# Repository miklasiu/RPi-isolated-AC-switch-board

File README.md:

# RPi isolated AC switch board
 24/110/230V AC triac switch board

The board is intended to be used as a garden watering control be me. Use for whatever you want yourselves. 
There is Python based software being developed thar runs on this hardware.
I used optotriac-trac because it is ~3 times less expenssive than cheapest relay and it should outlast any realy.
Triac introduces ~1.4V drop but it doesn't matter much for 24V and is negligible for 110V and up.

Borard can be made at home as a 1 side. All top-side connections can be made with wires. This is the way I did it.
For the Triac you can use BTA312. I was worried they won't trigger correctly with low voltage/current but they do without a problem.
I used BTA312-600 from WeEn but any low gate current, high voltage triac will likely work.

High side 10nF capacitor needs to be rated to peak-to-peak voltage (RMS_ACV*1.41). I used 500V ones.

I didn't use I2C eeprom at all. It was intended for RPi HAT configuration, but it works without it.

You can omit indicator LEDs and their resistors too.

Generally I put too much stuff here.

Oh there are 8 inputs for whatever use you wish inteded for dry contacts. NO VOLTAGE - just switches/contacts (water level, pressure)
And I2C connector with pinout for 0.91" OLED module. I don't use it too :).

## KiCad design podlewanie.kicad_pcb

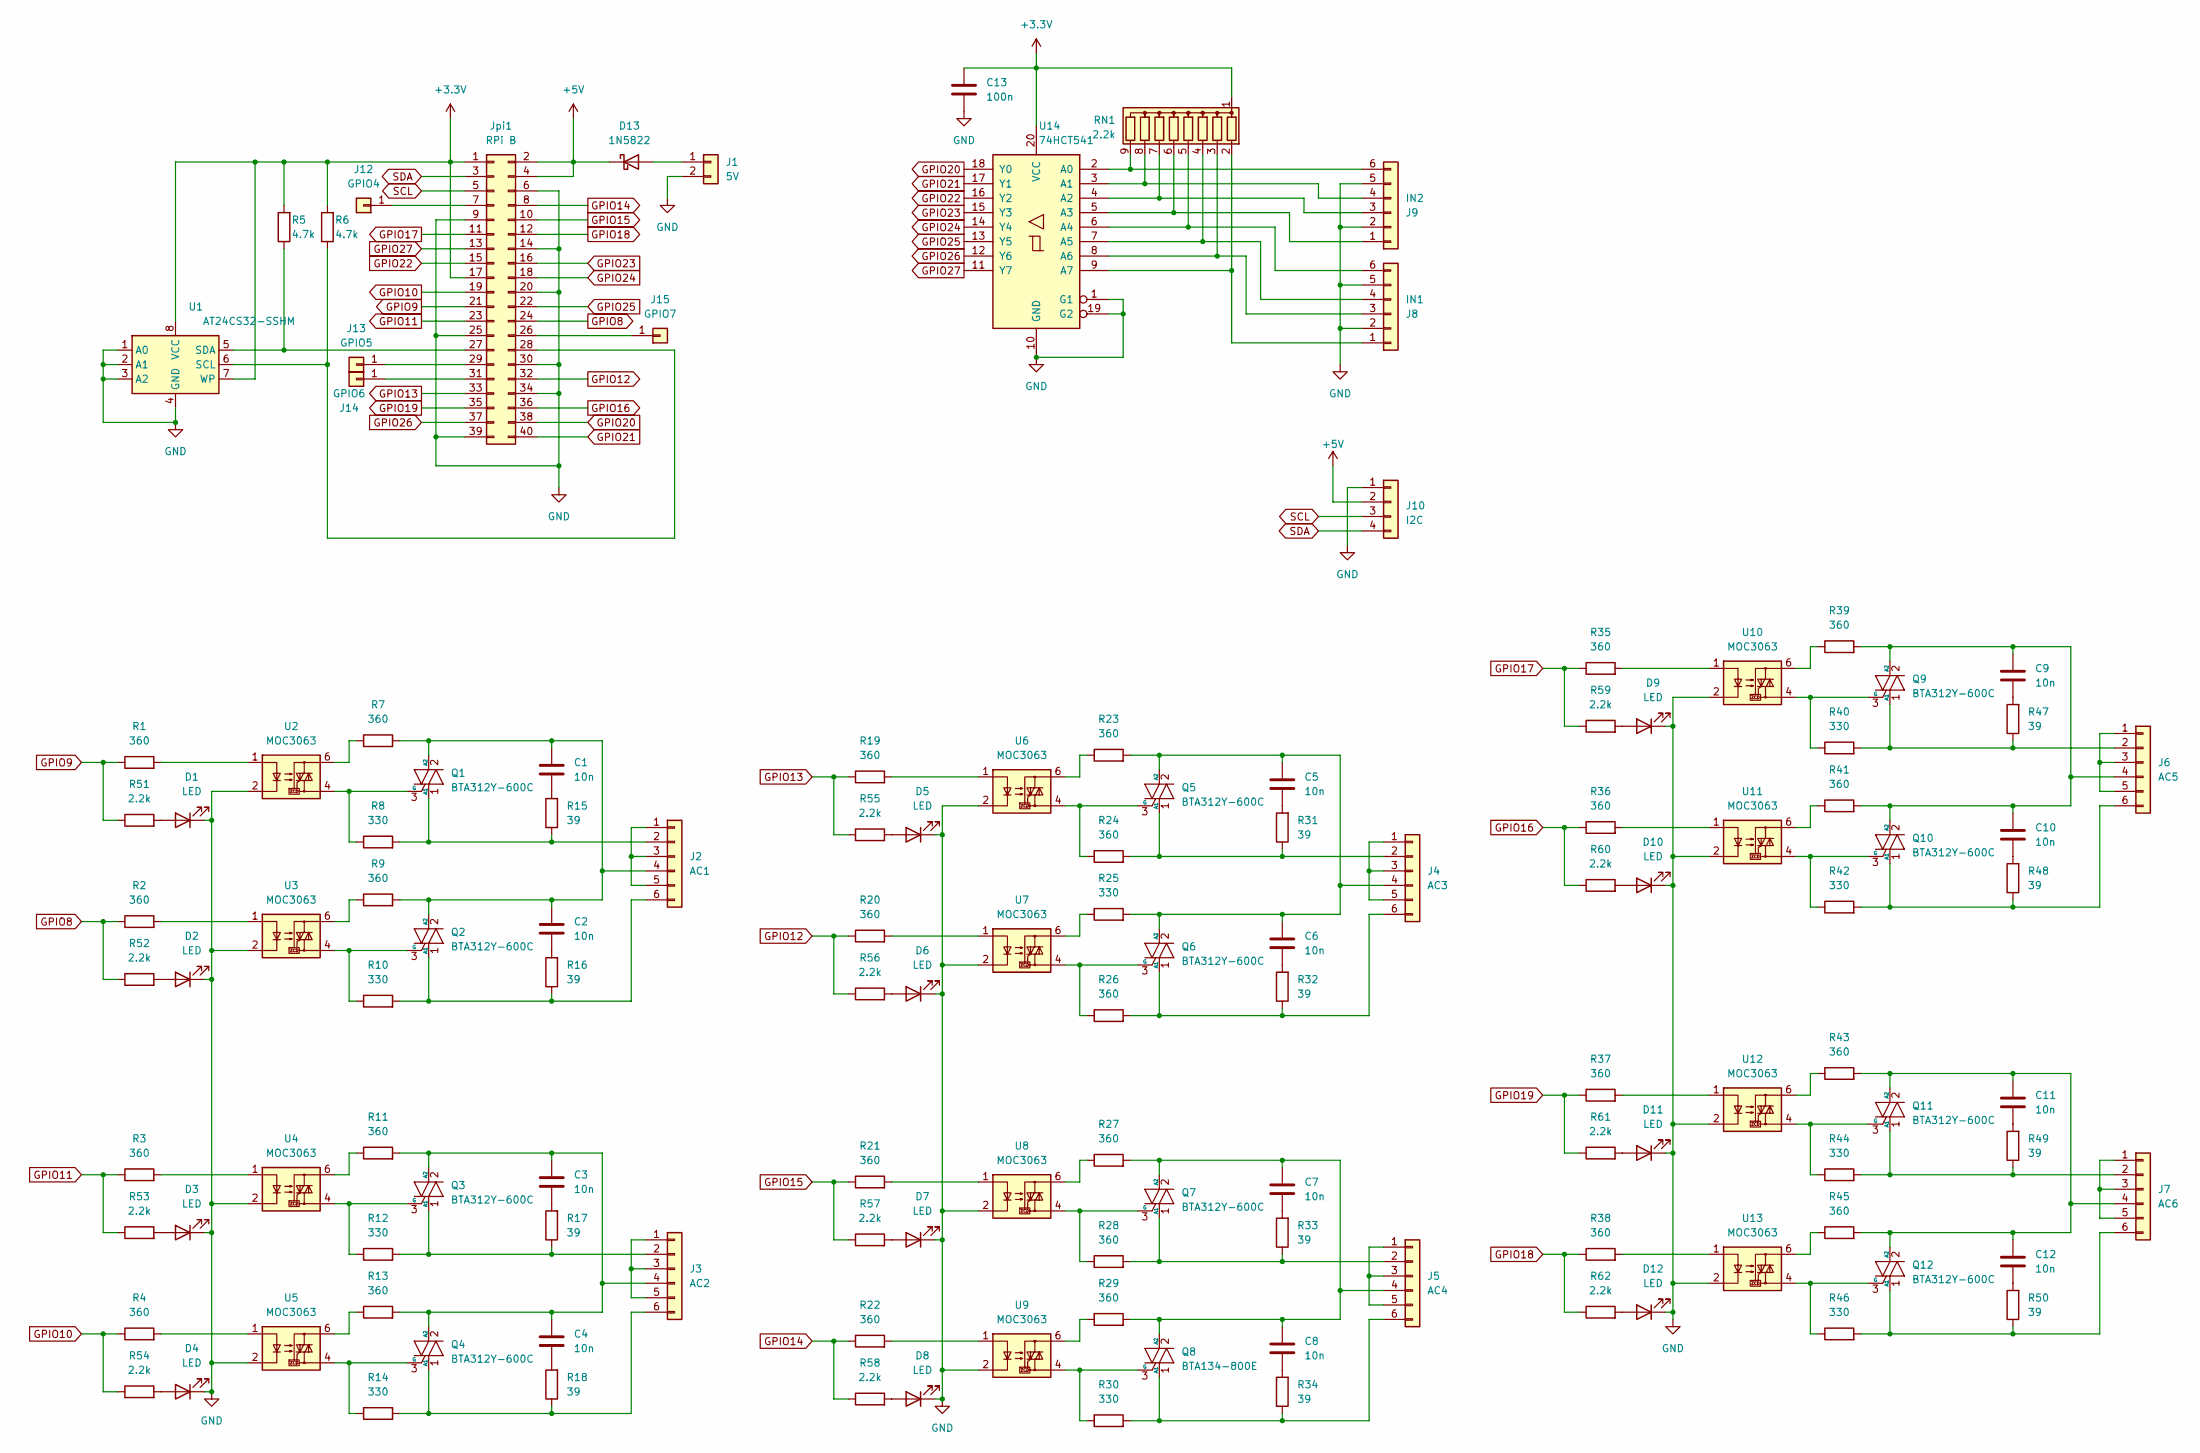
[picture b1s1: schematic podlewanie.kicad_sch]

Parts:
C1, C2, C3, C4, C5, C6, C7, C8, C9, C10, C11, C12: 10n; C_Disc_D9.0mm_W2.5mm_P5.00mm
C13: 100n; C_1206_3216Metric_Pad1.33x1.80mm_HandSolder
D1, D2, D3, D4, D5, D6, D7, D8, D9, D10, D11, D12: LED; LED_D3.0mm
D13: 1N5822; D_DO-201AD_P15.24mm_Horizontal
J1: 5V; Wago_734-162_1x02_P3.50mm_Horizontal
J2: AC1; Wago_734-166_1x06_P3.50mm_Horizontal
J3: AC2; Wago_734-166_1x06_P3.50mm_Horizontal
J4: AC3; Wago_734-166_1x06_P3.50mm_Horizontal
J5: AC4; Wago_734-166_1x06_P3.50mm_Horizontal
J6: AC5; Wago_734-166_1x06_P3.50mm_Horizontal
J7: AC6; Wago_734-166_1x06_P3.50mm_Horizontal
J8: IN1; Wago_734-166_1x06_P3.50mm_Horizontal
J9: IN2; Wago_734-166_1x06_P3.50mm_Horizontal
J10: I2C; PinSocket_1x04_P2.54mm_Vertical
J12: GPIO4; PinHeader_1x01_P2.54mm_Vertical
J13: GPIO5; PinHeader_1x01_P2.54mm_Vertical
J14: GPIO6; PinHeader_1x01_P2.54mm_Vertical
J15: GPIO7; PinHeader_1x01_P2.54mm_Vertical
Jpi1: RPi B; PinSocket_2x20_P2.54mm_Vertical
Q1, Q2, Q3, Q4, Q5, Q6, Q7, Q9, Q10, Q11, Q12: BTA312Y-600C; TO-220-3_Vertical
Q8: BTA134-800E; TO-220-3_Vertical
R1, R2, R3, R4, R7, R9, R11, R13, R19, R20, R21, R22, R23, R24, R26, R27, R28, R29, R35, R36, R37, R38, R39, R41, R43, R45: 360; R_1206_3216Metric_Pad1.30x1.75mm_HandSolder
R5, R6: 4.7k; R_1206_3216Metric_Pad1.30x1.75mm_HandSolder
R8, R10, R12, R14, R25, R30, R40, R42, R44, R46: 330; R_1206_3216Metric_Pad1.30x1.75mm_HandSolder
R15, R16, R17, R18, R31, R32, R33, R34, R47, R48, R49, R50: 39; R_1206_3216Metric_Pad1.30x1.75mm_HandSolder
R51, R52, R53, R54, R55, R56, R57, R58, R59, R60, R61, R62: 2.2k; R_1206_3216Metric_Pad1.30x1.75mm_HandSolder
RN1: 2.2k; R_Array_SIP9
U1: AT24CS32-SSHM; SOIC-8_3.9x4.9mm_P1.27mm
U2, U3, U4, U5, U6, U7, U8, U9, U10, U11, U12, U13: MOC3063; DIP-6_W10.16mm
U14: 74HCT541; SSOP-20_4.4x6.5mm_P0.65mm

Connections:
+3.3V: C13.1, Jpi1.1, Jpi1.17, R5.2, R6.2, RN1.1 (common), U1.7 (WP), U1.8 (VCC), U14.20 (VCC)
+5V: D13.1 (K), J10.2, Jpi1.2, Jpi1.4
GND: C13.2, D1.1 (K), D2.1 (K), D3.1 (K), D4.1 (K), D5.1 (K), D6.1 (K), D7.1 (K), D8.1 (K), D9.1 (K), D10.1 (K), D11.1 (K), D12.1 (K), J1.2, J8.2, J8.5, J9.2, J9.5, J10.1, Jpi1.6, Jpi1.9, Jpi1.14, Jpi1.20, Jpi1.25, Jpi1.30, Jpi1.34, Jpi1.39, U1.1 (A0), U1.2 (A1), U1.3 (A2), U1.4 (GND), U2.2, U3.2, U4.2, U5.2, U6.2, U7.2, U8.2, U9.2, U10.2, U11.2, U12.2, U13.2, U14.1 (G1), U14.10 (GND), U14.19 (G2)
GPIO8: Jpi1.24, R2.1, R52.1
GPIO9: Jpi1.21, R1.1, R51.1
GPIO10: Jpi1.19, R4.1, R54.1
GPIO11: Jpi1.23, R3.1, R53.1
GPIO12: Jpi1.32, R20.1, R56.1
GPIO13: Jpi1.33, R19.1, R55.1
GPIO14: Jpi1.8, R22.1, R58.1
GPIO15: Jpi1.10, R21.1, R57.1
GPIO16: Jpi1.36, R36.1, R60.1
GPIO17: Jpi1.11, R35.1, R59.1
GPIO18: Jpi1.12, R38.1, R62.1
GPIO19: Jpi1.35, R37.1, R61.1
GPIO20: Jpi1.38, U14.18 (Y0)
GPIO21: Jpi1.40, U14.17 (Y1)
GPIO22: Jpi1.15, U14.16 (Y2)
GPIO23: Jpi1.16, U14.15 (Y3)
GPIO24: Jpi1.18, U14.14 (Y4)
GPIO25: Jpi1.22, U14.13 (Y5)
GPIO26: Jpi1.37, U14.12 (Y6)
GPIO27: Jpi1.13, U14.11 (Y7)
unnamed: C1.2, R15.2
unnamed: C2.2, R16.2
unnamed: C3.2, R17.2
unnamed: C4.2, R18.2
unnamed: C5.2, R31.2
unnamed: C6.2, R32.2
unnamed: C7.2, R33.2
unnamed: C8.2, R34.2
unnamed: C9.2, R47.2
unnamed: C10.2, R48.2
unnamed: C11.2, R49.2
unnamed: C12.2, R50.2
unnamed: D1.2 (A), R51.2
unnamed: D2.2 (A), R52.2
unnamed: D3.2 (A), R53.2
unnamed: D4.2 (A), R54.2
unnamed: D5.2 (A), R55.2
unnamed: D6.2 (A), R56.2
unnamed: D7.2 (A), R57.2
unnamed: D8.2 (A), R58.2
unnamed: D9.2 (A), R59.2
unnamed: D10.2 (A), R60.2
unnamed: D11.2 (A), R61.2
unnamed: D12.2 (A), R62.2
unnamed: D13.2 (A), J1.1
unnamed: J2.1, J2.3, J2.5
unnamed: J2.2, Q1.1 (A1), R8.2, R15.1
unnamed: C1.1, C2.1, J2.4, Q1.2 (A2), Q2.2 (A2), R7.2, R9.2
unnamed: J2.6, Q2.1 (A1), R10.2, R16.1
unnamed: J3.1, J3.3, J3.5
unnamed: J3.2, Q3.1 (A1), R12.2, R17.1
unnamed: C3.1, C4.1, J3.4, Q3.2 (A2), Q4.2 (A2), R11.2, R13.2
unnamed: J3.6, Q4.1 (A1), R14.2, R18.1
unnamed: J4.1, J4.3, J4.5
unnamed: J4.2, Q5.1 (A1), R24.2, R31.1
unnamed: C5.1, C6.1, J4.4, Q5.2 (A2), Q6.2 (A2), R23.2, R25.2
unnamed: J4.6, Q6.1 (A1), R26.2, R32.1
unnamed: J5.1, J5.3, J5.5
unnamed: J5.2, Q7.1 (A1), R28.2, R33.1
unnamed: C7.1, C8.1, J5.4, Q7.2 (A2), Q8.2 (A2), R27.2, R29.2
unnamed: J5.6, Q8.1 (A1), R30.2, R34.1
unnamed: J6.1, J6.3, J6.5
unnamed: J6.2, Q9.1 (A1), R40.2, R47.1
unnamed: C9.1, C10.1, J6.4, Q9.2 (A2), Q10.2 (A2), R39.2, R41.2
unnamed: J6.6, Q10.1 (A1), R42.2, R48.1
unnamed: J7.1, J7.3, J7.5
unnamed: J7.2, Q11.1 (A1), R44.2, R49.1
unnamed: C11.1, C12.1, J7.4, Q11.2 (A2), Q12.2 (A2), R43.2, R45.2
unnamed: J7.6, Q12.1 (A1), R46.2, R50.1
unnamed: J8.1, RN1.2 (R1), U14.9 (A7)
unnamed: J8.3, RN1.3 (R2), U14.8 (A6)
unnamed: J8.4, RN1.4 (R3), U14.7 (A5)
unnamed: J8.6, RN1.5 (R4), U14.6 (A4)
unnamed: J9.1, RN1.6 (R5), U14.5 (A3)
unnamed: J9.3, RN1.7 (R6), U14.4 (A2)
unnamed: J9.4, RN1.8 (R7), U14.3 (A1)
unnamed: J9.6, RN1.9 (R8), U14.2 (A0)
unnamed: J12.1, Jpi1.7
unnamed: J13.1, Jpi1.29
unnamed: J14.1, Jpi1.31
unnamed: J15.1, Jpi1.26
unnamed: Jpi1.27, R5.1, U1.5 (SDA)
unnamed: Jpi1.28, R6.1, U1.6 (SCL)
unnamed: Q1.3 (G), R8.1, U2.4
unnamed: Q2.3 (G), R10.1, U3.4
unnamed: Q3.3 (G), R12.1, U4.4
unnamed: Q4.3 (G), R14.1, U5.4
unnamed: Q5.3 (G), R24.1, U6.4
unnamed: Q6.3 (G), R26.1, U7.4
unnamed: Q7.3 (G), R28.1, U8.4
unnamed: Q8.3 (G), R30.1, U9.4
unnamed: Q9.3 (G), R40.1, U10.4
unnamed: Q10.3 (G), R42.1, U11.4
unnamed: Q11.3 (G), R44.1, U12.4
unnamed: Q12.3 (G), R46.1, U13.4
unnamed: R1.2, U2.1
unnamed: R2.2, U3.1
unnamed: R3.2, U4.1
unnamed: R4.2, U5.1
unnamed: R7.1, U2.6
unnamed: R9.1, U3.6
unnamed: R11.1, U4.6
unnamed: R13.1, U5.6
unnamed: R19.2, U6.1
unnamed: R20.2, U7.1
unnamed: R21.2, U8.1
unnamed: R22.2, U9.1
unnamed: R23.1, U6.6
unnamed: R25.1, U7.6
unnamed: R27.1, U8.6
unnamed: R29.1, U9.6
unnamed: R35.2, U10.1
unnamed: R36.2, U11.1
unnamed: R37.2, U12.1
unnamed: R38.2, U13.1
unnamed: R39.1, U10.6
unnamed: R41.1, U11.6
unnamed: R43.1, U12.6
unnamed: R45.1, U13.6
SCL: J10.3, Jpi1.5
SDA: J10.4, Jpi1.3

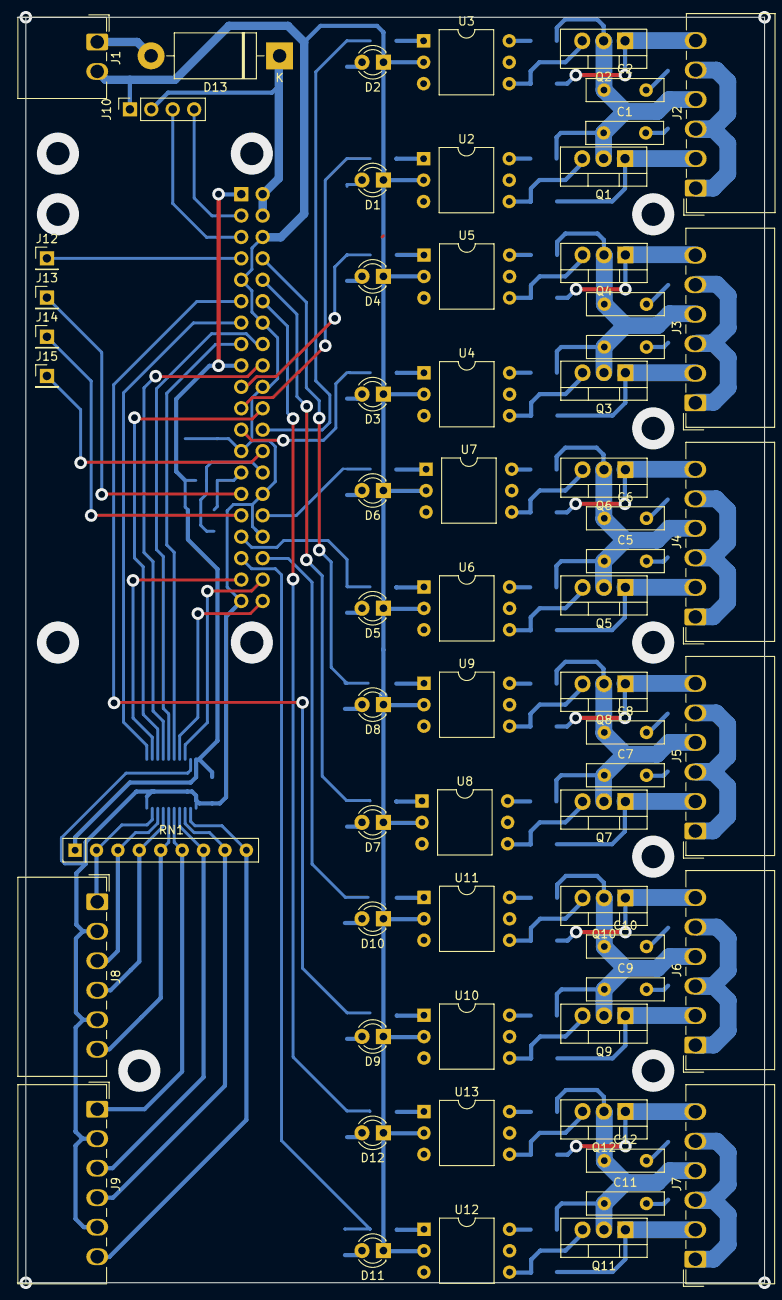
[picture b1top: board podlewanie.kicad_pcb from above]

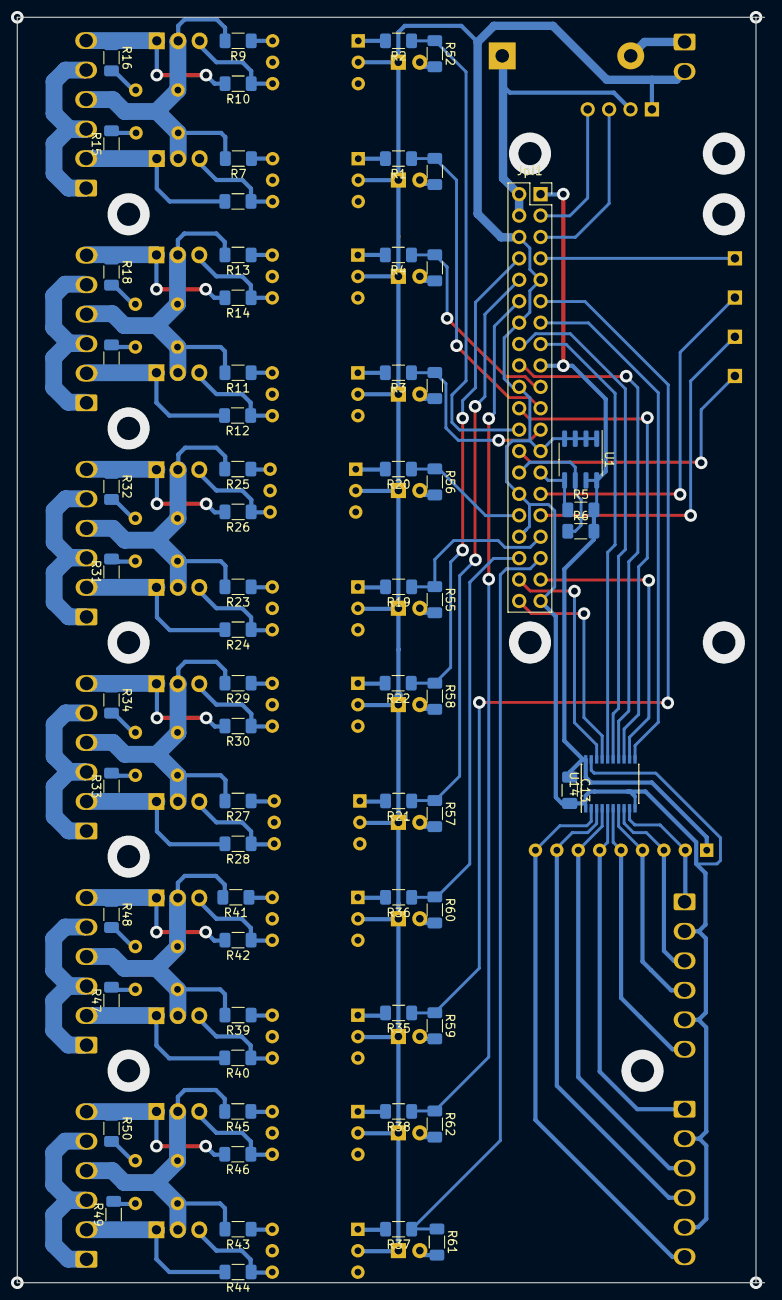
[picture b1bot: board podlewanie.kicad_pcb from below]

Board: 2 copper layers, 88.6 x 150.1 mm, 130 parts (66 on the bottom side), 124 nets.

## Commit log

2025-04-19 Initial
    The PCB I made.
2025-04-19 readme
